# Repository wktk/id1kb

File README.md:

# id1kb

## parts per 1 PCB

| Name | Value | Comment |
|----|----|----|
| Pro Micro | 1 | |
| SK6812MINI | 8 | Optional |
| Key Switch | 8 | |
| MJ-4PP-9 | 1 | Required only if connect two kbds |
| Diode 1N4148 | 8 | 100V 200mA, Also supports SMD |

## case

3D printable bottom case.

| File | Comment |
|----|----|
| case/id1kb_case.stl | Full floor |
| case/id1kb_case_truss.stl | Truss floor, less material |
| case/id1kb_case.scad | OpenSCAD source, adjust pin size etc. in Customizer |

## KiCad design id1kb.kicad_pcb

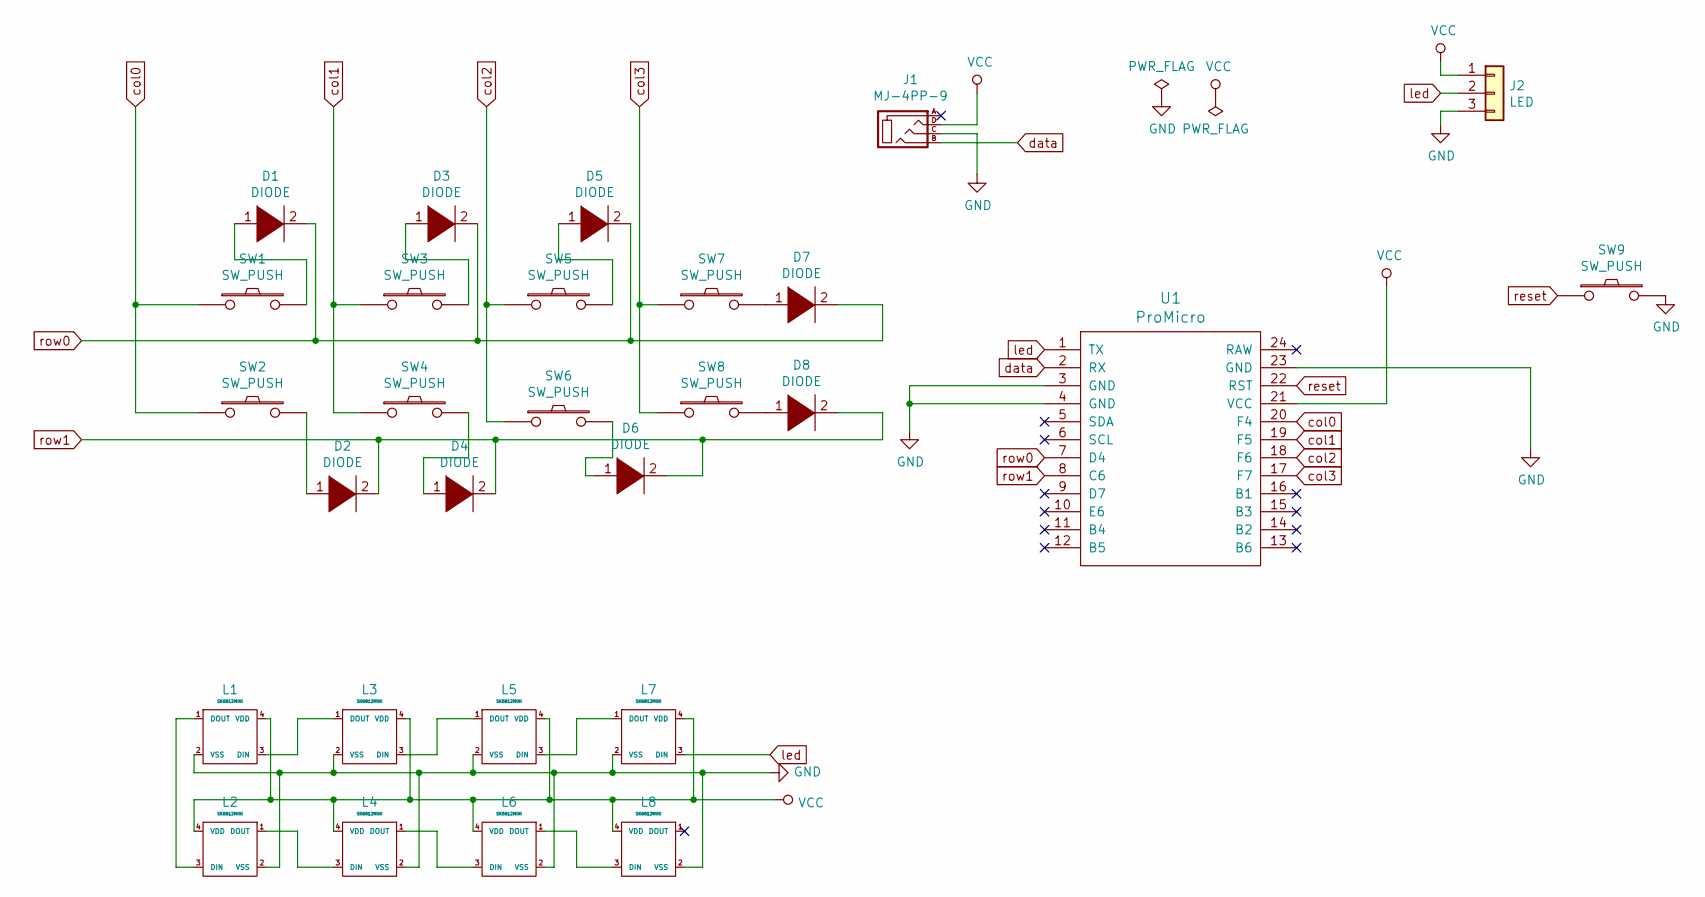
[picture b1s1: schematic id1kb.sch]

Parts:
D1, D2, D3, D4, D5, D6, D7, D8: DIODE; D3_TH_SMD
J1: MJ-4PP-9
J2: LED; StripLED_rev
L1, L2, L3, L4, L5, L6, L7, L8: SK6812MINI; SK6812MINI_rev
SW1, SW2, SW3, SW4, SW5, SW6, SW7, SW8: SW_PUSH; Hybrid_PCB_100H_Dual_hole
SW9: SW_PUSH; SW_Tactile_SPST_Angled_MJTP1117
U1: ProMicro; ArduinoProMicro-BackSide

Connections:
GND: J1.C, J2.3, L1.2 (VSS), L2.2 (VSS), L3.2 (VSS), L4.2 (VSS), L5.2 (VSS), L6.2 (VSS), L7.2 (VSS), L8.2 (VSS), SW9.2, U1.3 (GND), U1.4 (GND), U1.23 (GND); also elsewhere on the board
unnamed: D1.1 (K), SW1.2
unnamed: D2.1 (K), SW2.2
unnamed: D3.1 (K), SW3.2
unnamed: D4.1 (K), SW4.2
unnamed: D5.1 (K), SW5.2
unnamed: D6.1 (K), SW6.2
unnamed: D7.1 (K), SW7.2
unnamed: D8.1 (K), SW8.2
unnamed: L1.1 (DOUT), L2.3 (DIN)
unnamed: L1.3 (DIN), L3.1 (DOUT)
unnamed: L2.1 (DOUT), L4.3 (DIN)
unnamed: L3.3 (DIN), L5.1 (DOUT)
unnamed: L4.1 (DOUT), L6.3 (DIN)
unnamed: L5.3 (DIN), L7.1 (DOUT)
unnamed: L6.1 (DOUT), L8.3 (DIN)
unnamed 18: U1.5 (SDA); also elsewhere on the board
unnamed 19: U1.6 (SCL); also elsewhere on the board
unnamed 20: U1.9 (D7); also elsewhere on the board
unnamed 21: U1.10 (E6); also elsewhere on the board
unnamed 22: U1.11 (B4); also elsewhere on the board
unnamed 23: U1.12 (B5); also elsewhere on the board
unnamed 24: U1.13 (B6); also elsewhere on the board
unnamed 25: U1.14 (B2); also elsewhere on the board
unnamed 26: U1.15 (B3); also elsewhere on the board
unnamed 27: U1.16 (B1); also elsewhere on the board
unnamed 28: U1.24 (RAW); also elsewhere on the board
VCC: J1.D, J2.1, L1.4 (VDD), L2.4 (VDD), L3.4 (VDD), L4.4 (VDD), L5.4 (VDD), L6.4 (VDD), L7.4 (VDD), L8.4 (VDD), U1.21 (VCC); also elsewhere on the board
col0: SW1.1, SW2.1, U1.20 (F4); also elsewhere on the board
col1: SW3.1, SW4.1, U1.19 (F5); also elsewhere on the board
col2: SW5.1, SW6.1, U1.18 (F6); also elsewhere on the board
col3: SW7.1, SW8.1, U1.17 (F7); also elsewhere on the board
data: J1.B, U1.2 (RX); also elsewhere on the board
led: J2.2, L7.3 (DIN), U1.1 (TX); also elsewhere on the board
reset: SW9.1, U1.22 (RST); also elsewhere on the board
row0: D1.2 (A), D3.2 (A), D5.2 (A), D7.2 (A), U1.7 (D4); also elsewhere on the board
row1: D2.2 (A), D4.2 (A), D6.2 (A), D8.2 (A), U1.8 (C6); also elsewhere on the board

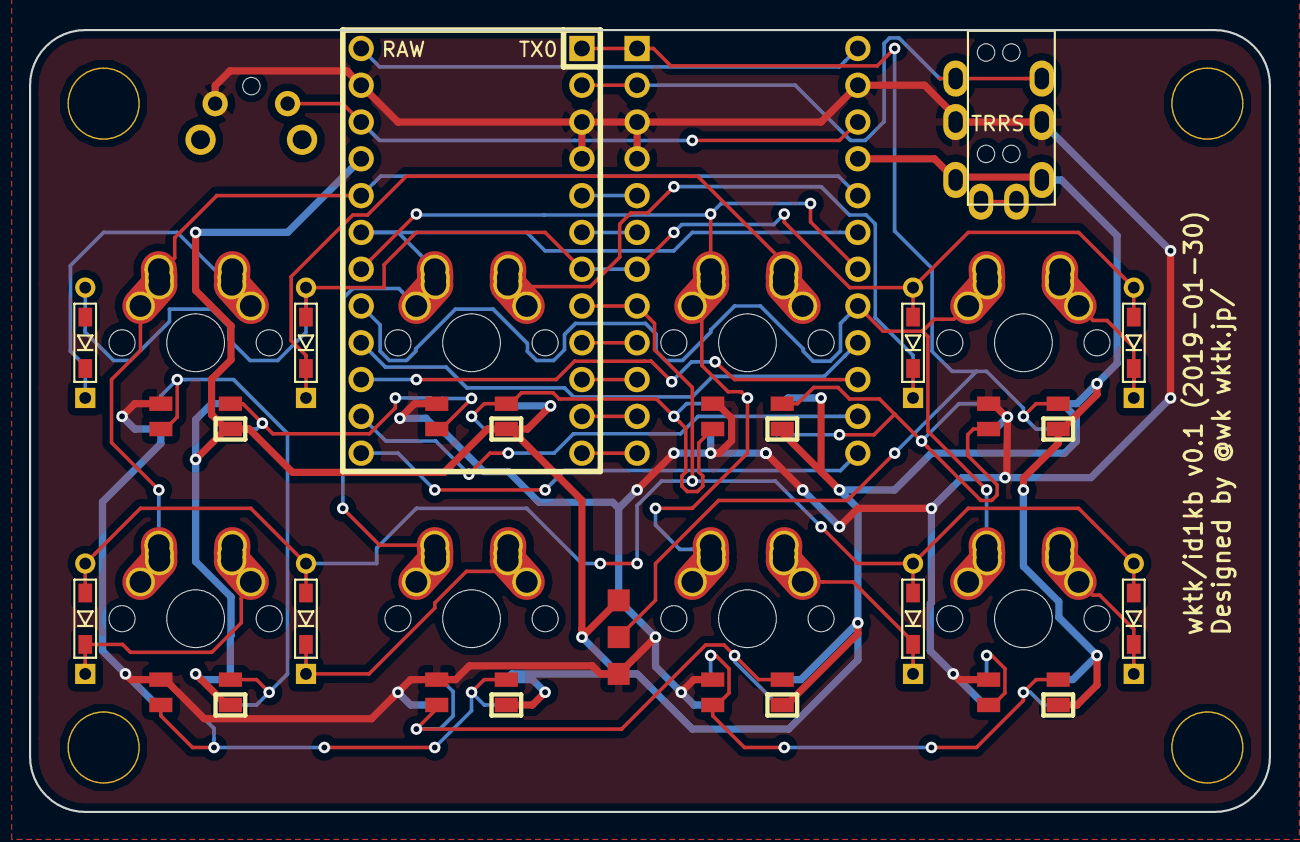
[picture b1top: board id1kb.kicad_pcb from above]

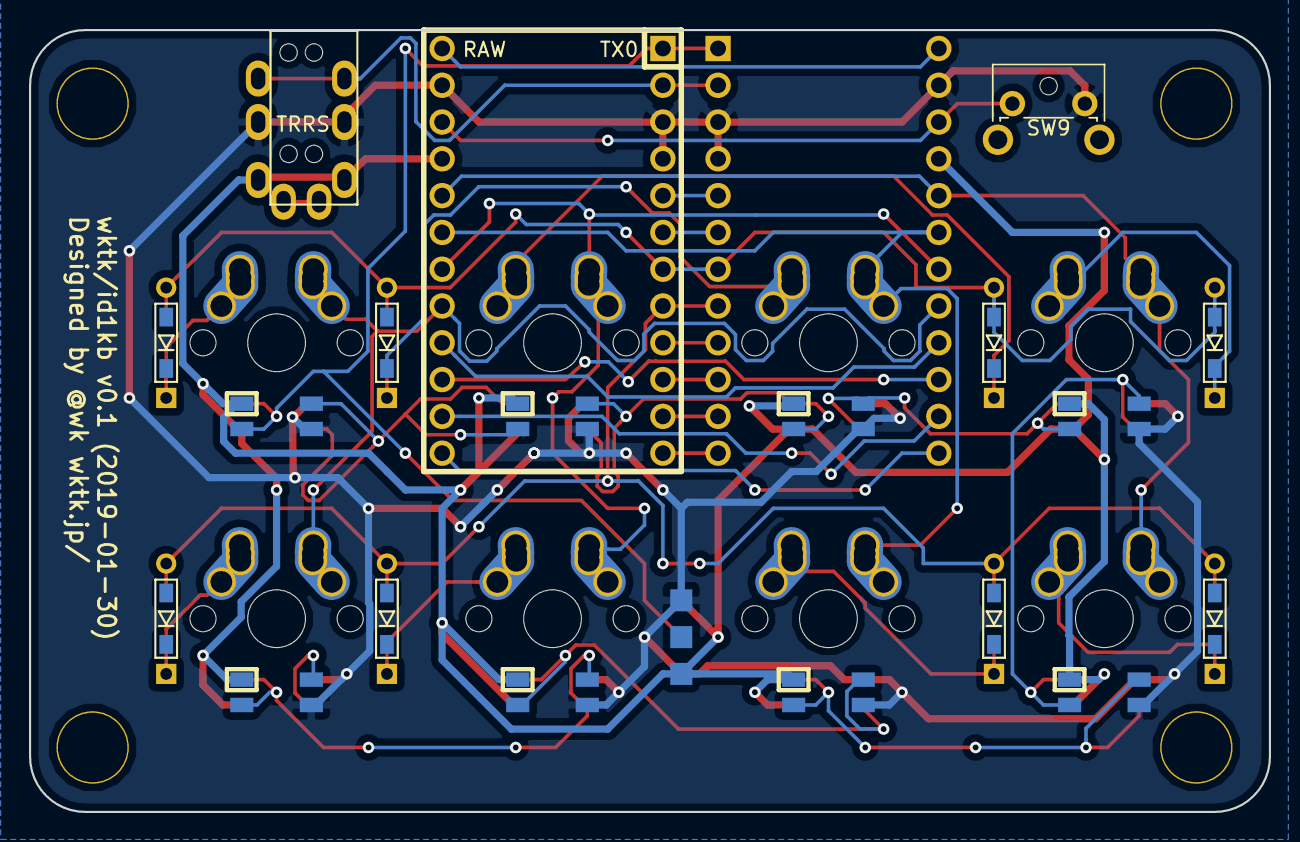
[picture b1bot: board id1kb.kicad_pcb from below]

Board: 2 copper layers, 85.6 x 54.0 mm, 33 parts (11 on the bottom side), 37 nets.

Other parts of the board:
Ref**: Val**; HOLE
Ref**#2, Ref**#3, Ref**#4: Val**; HOLE
U1#2: ProMicro; ArduinoProMicro-BackSide

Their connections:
GND: U1#2.3, U1#2.4, U1#2.23; also elsewhere on the board
unnamed 18: U1#2.5; also elsewhere on the board
unnamed 19: U1#2.6; also elsewhere on the board
unnamed 20: U1#2.9; also elsewhere on the board
unnamed 21: U1#2.10; also elsewhere on the board
unnamed 22: U1#2.11; also elsewhere on the board
unnamed 23: U1#2.12; also elsewhere on the board
unnamed 24: U1#2.13; also elsewhere on the board
unnamed 25: U1#2.14; also elsewhere on the board
unnamed 26: U1#2.15; also elsewhere on the board
unnamed 27: U1#2.16; also elsewhere on the board
unnamed 28: U1#2.24; also elsewhere on the board
VCC: U1#2.21; also elsewhere on the board
col0: U1#2.20; also elsewhere on the board
col1: U1#2.19; also elsewhere on the board
col2: U1#2.18; also elsewhere on the board
col3: U1#2.17; also elsewhere on the board
data: U1#2.2; also elsewhere on the board
led: U1#2.1; also elsewhere on the board
reset: U1#2.22; also elsewhere on the board
row0: U1#2.7; also elsewhere on the board
row1: U1#2.8; also elsewhere on the board

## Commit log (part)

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2019-01-27 配線の手前まで作成
2019-01-29 Pro micro の配置と回路の配線
2019-01-30 配線をリセット、ダイオードの位置をまとめた
2019-01-30 LED の回路を設定
2019-01-30 フットプリントを定義
2019-01-30 回路図の Pro Micro のフットプリントを Keebio の Backside 版に更新、PCB にフットプリントを全て反映
2019-01-30 LED を配置、ダイオードの位置を変更
2019-01-30 裏面 Pro Mirco が接続されていなかったので修正
2019-01-30 配置の順番がおかしくなっていたのを修正、Pro Micro を配線
2019-01-30 配線を済ませた
2019-01-30 余計なビアを削除
2019-01-30 スペーサの穴を確保
2019-01-30 GND の塗りつぶし
2019-01-30 Add credit
2019-01-30 余裕がありそうなのでクレカサイズに変更、配線位置を一部内側に
2019-01-30 GND を塗りつぶし
2019-01-30 保存して終了
2019-01-30 ガーバーファイルを生成
2019-01-30 SW5 の LED が結線できていなかったのを修正
2019-01-30 ガーバーを再生成
2019-01-30 塗りつぶしを再実行
2019-01-30 訂正前の ZIP を追加
2019-01-30 ZIP ファイルを更新
2019-01-31 Rename mykeyboard* => id1kb*
2019-02-11 Add README.md
2019-02-12 Describe parts
2019-02-12 Fix cache
